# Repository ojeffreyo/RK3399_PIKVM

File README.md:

# RK3399_PIKVM
Try to use RK3399 SoC to design a hardware tool kit resemble PIKVM.

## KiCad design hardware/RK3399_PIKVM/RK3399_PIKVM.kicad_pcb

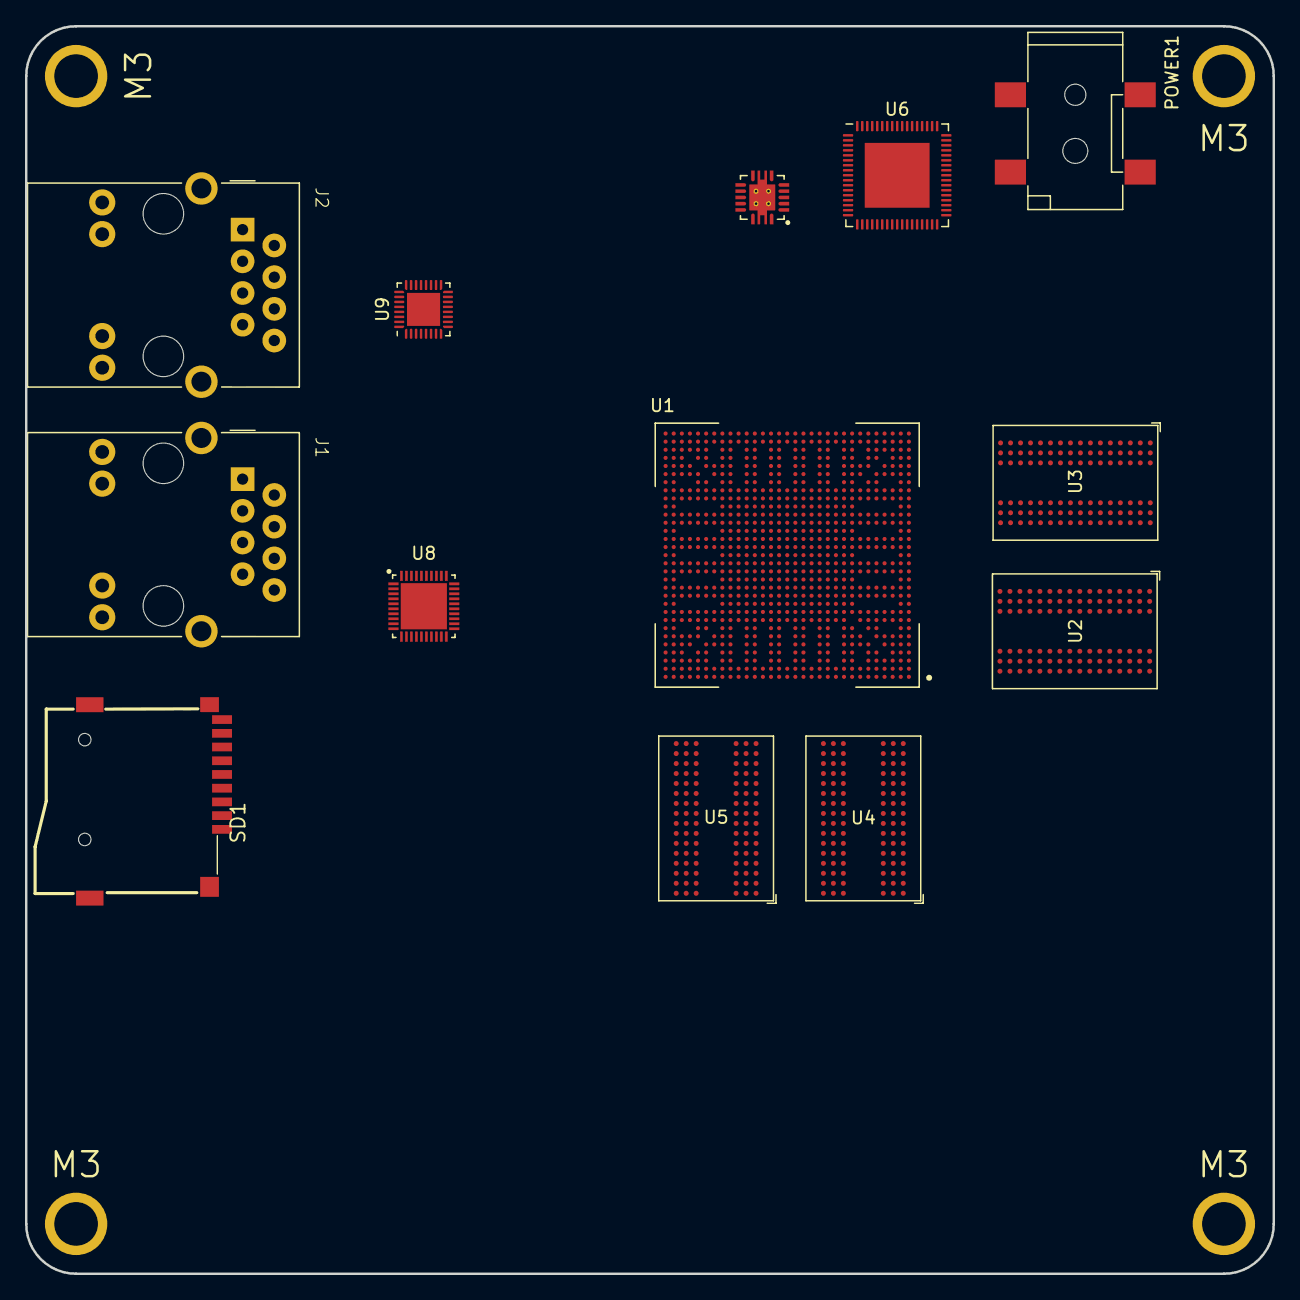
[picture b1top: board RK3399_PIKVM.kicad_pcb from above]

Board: 6 copper layers, 100.0 x 100.0 mm, 17 parts (0 on the bottom side), 49 nets, no tracks yet.

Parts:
J1, J2: HR911105A; RJ45_HanRun_HR911105A
M3, M3#2, M3#3, M3#4: M3_Whole
POWER1: DC-05-SMD-Connector; DC-05_SMD
SD1: TF-SMD_TF-01A
U1: RK3399
U2, U3, U4, U5: BGA-96_9.0x13.0mm_Layout2x3x16_P0.8mm
U6: QFN-68-1EP_8x8mm_P0.4mm_EP5.2x5.2mm
U7: TPS54821RHLR; TPS54821
U8: RTL8211F-CG; RTL8211_QFN40
U9: RTL8111H-CG; QFN-32-1EP_4x4mm_P0.4mm_EP2.65x2.65mm

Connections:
/DDR0_A0: U1.F2 (DDR0_A0), U2.N3 (A0), U3.N3 (A0)
/DDR0_A1: U1.F1 (DDR0_A1), U2.P7 (A1), U3.P7 (A1)
/DDR0_A2: U1.G1 (DDR0_A2), U2.P3 (A2), U3.P3 (A2)
/DDR0_A3: U1.G2 (DDR0_A3), U2.N2 (A3), U3.N2 (A3)
/DDR0_A4: U1.H2 (DDR0_A4), U2.P8 (A4), U3.P8 (A4)
/DDR0_A5: U1.H1 (DDR0_A5), U2.P2 (A5), U3.P2 (A5)
/DDR0_A6: U1.J1 (DDR0_A6), U2.R8 (A6), U3.R8 (A6)
/DDR0_A7: U1.J2 (DDR0_A7), U2.R2 (A7), U3.R2 (A7)
/DDR0_A8: U1.K2 (DDR0_A8), U2.T8 (A8), U3.T8 (A8)
/DDR0_A9: U1.K1 (DDR0_A9), U2.R3 (A9), U3.R3 (A9)
/DDR0_A10: U1.D1 (DDR0_A10), U2.L7 (A10), U3.L7 (A10)
/DDR0_A11: U1.E3 (DDR0_A11), U2.R7 (A11), U3.R7 (A11)
/DDR0_A12: U1.C1 (DDR0_A12), U2.N7 (A12), U3.N7 (A12)
/DDR0_A13: U1.D2 (DDR0_A13), U2.T3 (A13), U3.T3 (A13)
/DDR0_A14: U1.D3 (DDR0_A14), U2.T7 (A14), U3.T7 (A14)
/DDR0_A15: U1.H7 (DDR0_A15), U2.M7 (A15), U3.M7 (A15)
/DDR0_BA0: U1.C3 (DDR0_BA0), U2.M2 (BA0), U3.M2 (BA0)
/DDR0_BA1: U1.F4 (DDR0_BA1), U2.N8 (BA1), U3.N8 (BA1)
/DDR0_BA2: U1.M4 (DDR0_BA2), U2.M3 (BA2), U3.M3 (BA2)
/DDR1_A0: U1.B10 (DDR1_A0), U4.N3 (A0), U5.N3 (A0)
/DDR1_A1: U1.A10 (DDR1_A1), U4.P7 (A1), U5.P7 (A1)
/DDR1_A2: U1.B9 (DDR1_A2), U4.P3 (A2), U5.P3 (A2)
/DDR1_A3: U1.A9 (DDR1_A3), U4.N2 (A3), U5.N2 (A3)
/DDR1_A4: U1.B8 (DDR1_A4), U4.P8 (A4), U5.P8 (A4)
/DDR1_A5: U1.A8 (DDR1_A5), U4.P2 (A5), U5.P2 (A5)
/DDR1_A6: U1.B7 (DDR1_A6), U4.R8 (A6), U5.R8 (A6)
/DDR1_A7: U1.A7 (DDR1_A7), U4.R2 (A7), U5.R2 (A7)
/DDR1_A8: U1.B6 (DDR1_A8), U4.T8 (A8), U5.T8 (A8)
/DDR1_A9: U1.A6 (DDR1_A9), U4.R3 (A9), U5.R3 (A9)
/DDR1_A10: U1.A4 (DDR1_A10), U4.L7 (A10), U5.L7 (A10)
/DDR1_A11: U1.C5 (DDR1_A11), U4.R7 (A11), U5.R7 (A11)
/DDR1_A12: U1.A3 (DDR1_A12), U4.N7 (A12), U5.N7 (A12)
/DDR1_A13: U1.B4 (DDR1_A13), U4.T3 (A13), U5.T3 (A13)
/DDR1_A14: U1.C4 (DDR1_A14), U4.T7 (A14), U5.T7 (A14)
/DDR1_A15: U1.G8 (DDR1_A15), U4.M7 (A15), U5.M7 (A15)
/DDR1_BA0: U1.B2 (DDR1_BA0), U4.M2 (BA0), U5.M2 (BA0)
/DDR1_BA1: U1.D6 (DDR1_BA1), U4.N8 (BA1), U5.N8 (BA1)
/DDR1_BA2: U1.D12 (DDR1_BA2), U4.M3 (BA2), U5.M3 (BA2)
unnamed: U1.L9 (DDR0_VDD_1), U1.L10 (DDR0_VDD_2), U1.M9 (DDR0_VDD_3), U1.N9 (DDR0_VDD_4), U1.N10 (DDR0_VDD_5), U1.P9 (DDR0_VDD_6), U1.R9 (DDR0_VDD_7)
unnamed: U1.R10 (DDR0_VDD_8), U1.T9 (DDR0_VDD_9), U1.U9 (DDR0_VDD_10), U1.U10 (DDR0_VDD_11), U1.V9 (DDR0_VDD_12)
unnamed: U1.J11 (DDR1_VDD_1), U1.J12 (DDR1_VDD_2), U1.J13 (DDR1_VDD_3), U1.J14 (DDR1_VDD_4), U1.J15 (DDR1_VDD_5), U1.J16 (DDR1_VDD_6), U1.J17 (DDR1_VDD_7)
unnamed: U1.J18 (DDR1_VDD_8), U1.K11 (DDR1_VDD_9), U1.K13 (DDR1_VDD_10), U1.K15 (DDR1_VDD_11), U1.K17 (DDR1_VDD_12)
unnamed: U2.B2 (VDD#3), U2.D9 (VDD#7), U2.G7 (VDD#5), U2.K2 (VDD#4), U2.K8 (VDD#6), U2.N1 (VDD#1), U2.N9 (VDD#8), U2.R1 (VDD#2), U2.R9 (VDD#9)
unnamed: U3.B2 (VDD#3), U3.D9 (VDD#7), U3.G7 (VDD#5), U3.K2 (VDD#4), U3.K8 (VDD#6), U3.N1 (VDD#1), U3.N9 (VDD#8), U3.R1 (VDD#2), U3.R9 (VDD#9)
unnamed: U4.B2 (VDD#3), U4.D9 (VDD#7), U4.G7 (VDD#5), U4.K2 (VDD#4), U4.K8 (VDD#6), U4.N1 (VDD#1), U4.N9 (VDD#8), U4.R1 (VDD#2), U4.R9 (VDD#9)
unnamed: U4.A1 (VDDQ#1), U4.A8 (VDDQ#6), U4.C1 (VDDQ#2), U4.C9 (VDDQ#9), U4.D2 (VDDQ#4), U4.E9 (VDDQ#8), U4.F1 (VDDQ#3), U4.H2 (VDDQ#5), U4.H9 (VDDQ#7)
unnamed: U5.B2 (VDD#3), U5.D9 (VDD#7), U5.G7 (VDD#5), U5.K2 (VDD#4), U5.K8 (VDD#6), U5.N1 (VDD#1), U5.N9 (VDD#8), U5.R1 (VDD#2), U5.R9 (VDD#9)
unnamed: U5.A1 (VDDQ#1), U5.A8 (VDDQ#6), U5.C1 (VDDQ#2), U5.C9 (VDDQ#9), U5.D2 (VDDQ#4), U5.E9 (VDDQ#8), U5.F1 (VDDQ#3), U5.H2 (VDDQ#5), U5.H9 (VDDQ#7)
VSS: U1.A1 (VSS_1), U1.A27 (VSS_2), U1.A31 (VSS_3), U1.AA3 (VSS_4), U1.AA5 (VSS_5), U1.AA9 (VSS_6), U1.AA10 (VSS_179), U1.AA11 (AVSS_13), U1.AA12 (AVSS_17), U1.AA13 (VSS_177), U1.AA14 (AVSS_26), U1.AA15 (AVSS_53), U1.AA23 (AVSS_4), U1.AA26 (AVSS_6), U1.AA29 (AVSS_7), U1.AB9 (VSS_9), U1.AB10 (AVSS_12), U1.AB11 (AVSS_8), U1.AB13 (AVSS_9), U1.AB15 (AVSS_42), U1.AB16 (AVSS_41), U1.AB17 (AVSS_52), U1.AB19 (VSS_140), U1.AB23 (AVSS_5), U1.AC3 (VSS_16), U1.AC11 (AVSS_44), U1.AC13 (AVSS_45), U1.AC15 (AVSS_10), U1.AC16 (AVSS_18), U1.AC17 (AVSS_43), U1.AC18 (VSS_145), U1.AC20 (VSS_13), U1.AC21 (VSS_132), U1.AC22 (VSS_12), U1.AC23 (AVSS_19), U1.AC25 (AVSS_51), U1.AC26 (AVSS_14), U1.AC29 (AVSS_15), U1.AD3 (VSS_17), U1.AD5 (VSS_18), U1.AD10 (VSS_19), U1.AD13 (AVSS_11), U1.AD17 (AVSS_16), U1.AD21 (VSS_163), U1.AD22 (VSS_11), U1.AD26 (AVSS_40), U1.AD29 (AVSS_20), U1.AE11 (AVSS_21), U1.AE12 (AVSS_22), U1.AE14 (AVSS_23), U1.AE17 (AVSS_24), U1.AE23 (VSS_14), U1.AE27 (AVSS_25), U1.AF9 (VSS_20), U1.AF17 (AVSS_27), U1.AF18 (VSS_7), U1.AF20 (VSS_10), U1.AF23 (AVSS_2), U1.AF24 (AVSS_3), U1.AF29 (AVSS_28), U1.AG2 (VSS_21), U1.AG29 (AVSS_29), U1.AH29 (AVSS_30), U1.AJ5 (VSS_22), U1.AJ6 (AVSS_31), U1.AJ8 (AVSS_32), U1.AJ9 (AVSS_33), U1.AJ11 (AVSS_34), U1.AJ12 (AVSS_35), U1.AJ14 (AVSS_36), U1.AJ15 (AVSS_37), U1.AJ17 (AVSS_38), U1.AJ18 (AVSS_39), U1.AJ20 (VSS_180), U1.AJ21 (VSS_172), U1.AJ23 (VSS_173), U1.AJ24 (VSS_174), U1.AJ26 (VSS_175), U1.AJ27 (VSS_176), U1.AJ28 (VSS_171), U1.AJ29 (AVSS_47), U1.AL1 (VSS_23), U1.AL31 (VSS_178), U1.B5 (VSS_24), U1.C8 (VSS_25), U1.C9 (VSS_26), U1.C11 (VSS_27), U1.C12 (VSS_28), U1.C14 (VSS_29), U1.C15 (VSS_30), U1.C17 (VSS_31), U1.C18 (VSS_32), U1.C20 (VSS_33), U1.C21 (VSS_34), U1.C23 (VSS_35), U1.C24 (VSS_36), U1.C26 (VSS_37), U1.D5 (VSS_38), U1.E2 (VSS_39), U1.E4 (VSS_40), U1.E7 (VSS_41), U1.E12 (VSS_42), U1.E15 (VSS_43), U1.E18 (VSS_44), U1.E21 (VSS_45), U1.E24 (VSS_46), U1.E31 (VSS_47), U1.F8 (VSS_48), U1.F15 (VSS_49), U1.F18 (VSS_50), U1.F20 (VSS_51), U1.F21 (VSS_52), U1.G5 (VSS_53), U1.G9 (VSS_54), U1.G18 (VSS_55), U1.G27 (VSS_56), U1.H3 (VSS_57), U1.H9 (VSS_58), U1.H10 (VSS_59), U1.H11 (VSS_60), U1.H12 (VSS_61), U1.H13 (VSS_62), U1.H15 (VSS_63), U1.H16 (VSS_64), U1.H17 (VSS_65), U1.H18 (VSS_66), U1.H26 (VSS_67), U1.J3 (VSS_68), U1.J6 (VSS_69), U1.J7 (VSS_70), U1.J8 (VSS_71), U1.J9 (VSS_72), U1.J10 (VSS_73), U1.K8 (VSS_74), U1.K9 (VSS_75), U1.K10 (VSS_76), U1.K12 (VSS_77), U1.K14 (VSS_78), U1.K16 (VSS_79), U1.K18 (VSS_80), U1.K20 (VSS_82), U1.K22 (VSS_84), U1.L3 (VSS_85), U1.L6 (VSS_86), U1.L8 (VSS_87), U1.L11 (VSS_88), U1.L12 (VSS_89), U1.L13 (VSS_90), U1.L14 (VSS_91), U1.L15 (VSS_92), U1.L16 (VSS_93), U1.L20 (VSS_96), U1.L22 (VSS_97), U1.L27 (VSS_99), U1.M3 (VSS_100), U1.M8 (VSS_101), U1.M10 (VSS_102), U1.M16 (VSS_103), U1.M23 (VSS_104), U1.N8 (VSS_105), U1.N13 (VSS_108), U1.N14 (VSS_109), U1.N15 (VSS_110), U1.N16 (VSS_111), U1.N17 (VSS_94), U1.N19 (VSS_83), U1.N21 (VSS_98), U1.P3 (VSS_112), U1.P6 (VSS_113), U1.P7 (VSS_114), U1.P8 (VSS_115), U1.P10 (VSS_116), U1.P11 (VSS_106), U1.P12 (VSS_107), U1.P16 (VSS_117), U1.P19 (VSS_119), U1.P21 (VSS_121), U1.R3 (VSS_123), U1.R5 (VSS_124), U1.R6 (VSS_125), U1.R14 (VSS_129), U1.R15 (VSS_130), U1.R16 (VSS_131), U1.R18 (VSS_165), U1.R21 (VSS_120), U1.R23 (VSS_133), U1.T8 (VSS_134), U1.T10 (VSS_135), U1.T16 (VSS_138), U1.T18 (VSS_168), U1.T19 (VSS_122), U1.T21 (VSS_139), U1.U3 (VSS_141), U1.U8 (VSS_142), U1.U11 (VSS_126), U1.U12 (VSS_127), U1.U14 (VSS_137), U1.U15 (VSS_143), U1.U16 (VSS_144), U1.U19 (VSS_146), U1.U21 (VSS_147), U1.U22 (VSS_149), U1.U23 (AVSS_49), U1.U29 (VSS_150), U1.V3 (VSS_151), U1.V5 (VSS_152), U1.V8 (VSS_153), U1.V10 (VSS_154), U1.V17 (VSS_148), U1.V23 (AVSS_50), U1.W8 (VSS_161), U1.W9 (VSS_162), U1.W13 (VSS_128), U1.W17 (VSS_159), U1.W18 (VSS_169), U1.W19 (VSS_167), U1.W21 (VSS_81), U1.W22 (VSS_158), U1.W23 (AVSS_46), U1.W30 (VSS_160), U1.Y3 (VSS_8), U1.Y9 (VSS_166), U1.Y10 (VSS_15), U1.Y11 (VSS_155), U1.Y12 (VSS_136), U1.Y13 (VSS_164), U1.Y14 (VSS_156), U1.Y15 (VSS_157), U1.Y16 (VSS_118), U1.Y17 (VSS_95), U1.Y20 (VSS_170), U1.Y23 (AVSS_1), U1.Y29 (AVSS_48), U2.A9 (VSS#9), U2.B1 (VSSQ#1), U2.B3 (VSS#6), U2.B9 (VSSQ#7), U2.D1 (VSSQ#2), U2.D8 (VSSQ#5), U2.E1 (VSS#1), U2.E2 (VSSQ#4), U2.E8 (VSSQ#6), U2.F9 (VSSQ#8), U2.G1 (VSSQ#3), U2.G8 (VSS#7), U2.G9 (VSSQ#9), U2.J2 (VSS#5), U2.J8 (VSS#8), U2.M1 (VSS#2), U2.M9 (VSS#10), U2.P1 (VSS#3), U2.P9 (VSS#11), U2.T1 (VSS#4), U2.T9 (VSS#12), U3.A9 (VSS#9), U3.B1 (VSSQ#1), U3.B3 (VSS#6), U3.B9 (VSSQ#7), U3.D1 (VSSQ#2), U3.D8 (VSSQ#5), U3.E1 (VSS#1), U3.E2 (VSSQ#4), U3.E8 (VSSQ#6), U3.F9 (VSSQ#8), U3.G1 (VSSQ#3), U3.G8 (VSS#7), U3.G9 (VSSQ#9), U3.J2 (VSS#5), U3.J8 (VSS#8), U3.M1 (VSS#2), U3.M9 (VSS#10), U3.P1 (VSS#3), U3.P9 (VSS#11), U3.T1 (VSS#4), U3.T9 (VSS#12), U4.A9 (VSS#9), U4.B1 (VSSQ#1), U4.B3 (VSS#6), U4.B9 (VSSQ#7), U4.D1 (VSSQ#2), U4.D8 (VSSQ#5), U4.E1 (VSS#1), U4.E2 (VSSQ#4), U4.E8 (VSSQ#6), U4.F9 (VSSQ#8), U4.G1 (VSSQ#3), U4.G8 (VSS#7), U4.G9 (VSSQ#9), U4.J2 (VSS#5), U4.J8 (VSS#8), U4.M1 (VSS#2), U4.M9 (VSS#10), U4.P1 (VSS#3), U4.P9 (VSS#11), U4.T1 (VSS#4), U4.T9 (VSS#12), U5.A9 (VSS#9), U5.B1 (VSSQ#1), U5.B3 (VSS#6), U5.B9 (VSSQ#7), U5.D1 (VSSQ#2), U5.D8 (VSSQ#5), U5.E1 (VSS#1), U5.E2 (VSSQ#4), U5.E8 (VSSQ#6), U5.F9 (VSSQ#8), U5.G1 (VSSQ#3), U5.G8 (VSS#7), U5.G9 (VSSQ#9), U5.J2 (VSS#5), U5.J8 (VSS#8), U5.M1 (VSS#2), U5.M9 (VSS#10), U5.P1 (VSS#3), U5.P9 (VSS#11), U5.T1 (VSS#4), U5.T9 (VSS#12)

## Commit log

2023-05-15 Update some datasheets.
2023-05-15 Finished the selection for SRAM and power IC.
2023-05-15 Update hardware project and design specification.
2023-05-15 Update some footprint and datasheets.
2023-05-16 Did some fan-out layout test, add some basic PCB layout rules.
2023-05-16 Updated SFF-8611 port specification and some 3D models.
2023-05-16 Made a testing design.
2023-05-16 Try to add PCIE-Mini port to the board.
2023-05-16 Updated.
2023-05-17 Did little modification.
2023-05-17 Did some layout practice.
2023-05-18 Updated some REF design.
2023-05-18 Use RTL8211 as the ETH PHY.
2023-05-19 Updated SRAM symbol
2023-05-20 Updated RK3399 symbol.
2023-05-21 Updated schematics.
2023-05-21 Updated schematic.
2023-05-21 Finished the function allocation.
2023-05-21 Updated the schematic again.
2023-05-22 Updated schematic
2023-05-24 Updated some datasheets and ref PDFs
2023-05-24 Updated datasheets.
2023-05-25 Updated some contents
